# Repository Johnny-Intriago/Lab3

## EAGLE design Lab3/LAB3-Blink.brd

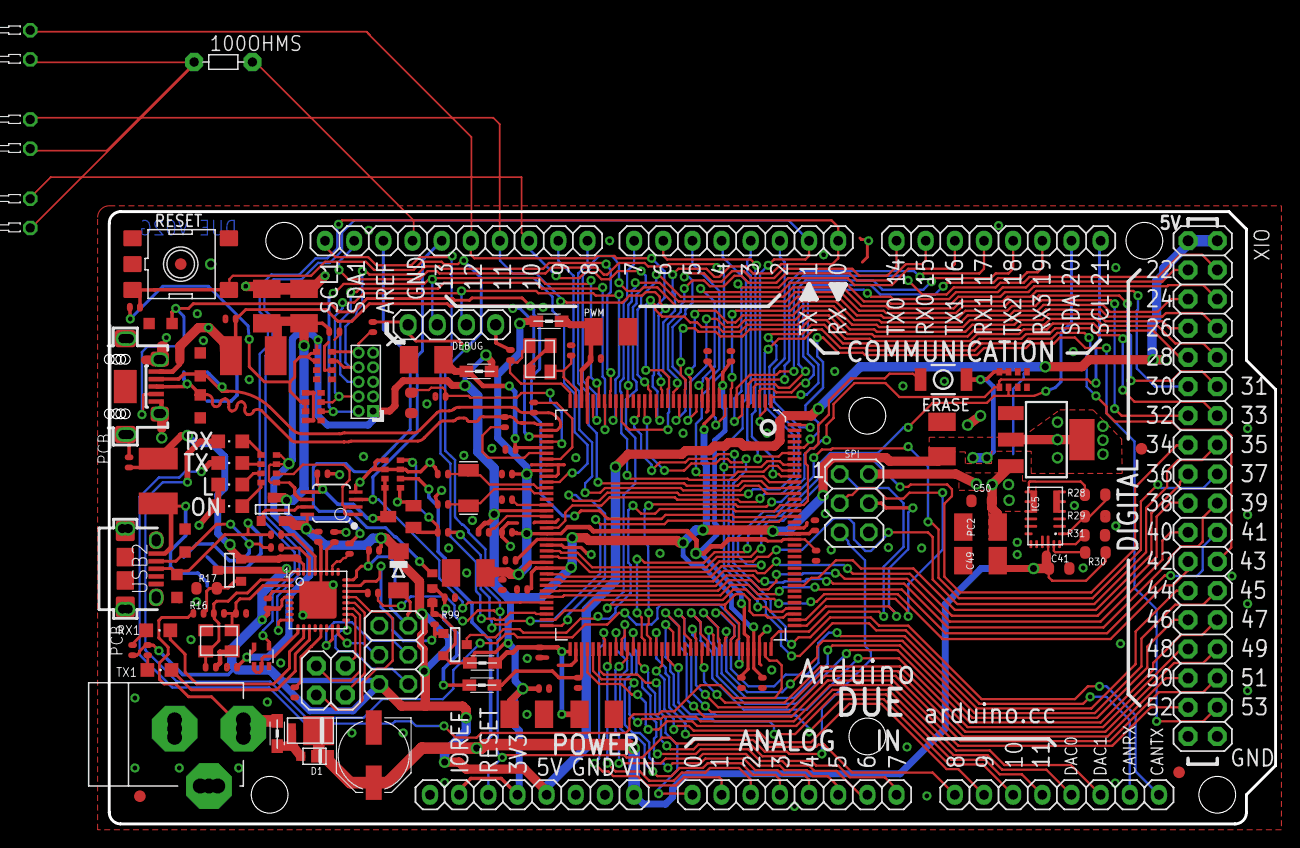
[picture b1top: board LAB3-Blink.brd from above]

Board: 2 copper layers, 101.6 x 53.3 mm, 145 parts (0 on the bottom side), 150 nets.

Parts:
100OHMS: 100; R-5
ADCH: FH254-108DF08500V; 1X08
ADCL: FH254-108DF08500V; 1X08
BR1: NM; J0402
C1, C2, C3, C11, C27, C29, C33, C35, C49: 22uF; SMC_B
C4, C5, C6, C7, C8, C9, C10, C12, C13, C14, C15, C16, C17, C18, C19, C28, C30, C31, C32, C34, C36, C37: 100nF; C0402
C20, C26: 10n; C0402
C21, C22, C23, C24, C25, C39, C40: 22pF; C0402
C38: 1uF; C0402
C41, C50: 100nF; C0603-ROUND
CN2: PINHEAD-2x5-P1.27; PINHEAD_2X05_127
COMMUNICATION: FH254-108DF08500V; 1X08
D1: MSS1P3L-M3/89A; MICROSMP
D2: CD1206-S01575; MINIMELF
D5: SS1P3L; DO220AAL
DEBUG: PH1X4-THT
E$1, E$2, E$3: LED3MM_H7,5MM
ERASE: 157SW; SMD_157SW
F1, F2: MF-MSMF050-2 500mA; L1812
FID1, FID2, FID3, FID4: FIDUCIALMOUNT; FIDUCIA-MOUNT
IC1: LMV358IDGKR; MSOP08
IC4: NX1117CE33Z; SOT223
IC5: MPM3610; QFN-20
IC6: ATMEGA16U2-MU; MLF32
IC10: 74LVC1G125DCKR; SC70-5
ICSP1: ICSP; 2X03
JP5: 2x2M - NM; 2X02
JR1: 0R; R0402
L: Yellow; CHIPLED_0805
L1, L2, L3, L5, L6: MH2029-300Y; 0805
ON: Green; CHIPLED_0805
PC1: 47uF; PANASONIC_D
PC2: 22uF; SMC_B
POWER: FH254-108DF08500V; 1X08
PWMH: FH254-110DF08500V; 1X10
PWML: FH254-108DF08500V; 1X08
Q2: BC847B; SOT23
R1, R8: 0R; R0402
R2, R13, R18, R99: 10K; R0402
R3, R14, R15, R21, R23: 1K; R0402
R4, R16: 100k; R0402
R5, R6: 39R 1%; R0402
R7: 6K8; R0603-ROUND
R9: 1M; R0402
R17: 75K; R0603-ROUND
R19, R20: 22R; R0402
R28: 100K_1%; R0603-ROUND
R29: 19K1_0,1%; R0603-ROUND
R30: 100k; R0603-ROUND
R31: 56k; R0603-ROUND
RESET: TS42
RN1, RN2, RN4: 100k; CAY16
RN3: 1K; CAY16
RN5: 1K5; CAY16
RX, RX1: Yellow; CHIPLED_0805
SPI: ICSP; 2X03
T1, T2, T3: PMV48XP; SOT-23
TX, TX1: Yellow; CHIPLED_0805
U1: ATSAM3X8EA-AU; LQFP144
U$1, U$2: DNP; FRAME
UD+1, UD+2: DNP; TP-1.00MM
UD-1, UD-2: DNP; TP-1.00MM
UGND1, UGND2: DNP; TP-1.00MM
USB1: MCR-AB1-S-RA-SMT-TR; MCR-AB1-S-RA-SMT
USB2: MCR-B-S-RA-SMT-CS1TR; CON2_USB_MICRO_B_AT
UVB1, UVB2: DNP; TP-1.00MM
X2: POWER-SUPPLY; POWERSUPPLY_DC-21MM
XIO: 18x2F-H8.5; 2X18
Y1: 12mHz-12pF-K7; CRYSTAL-3.2-2.5
Y2: 32,768Khz_SMD; RESONATOR_EPSON_FC_145
Y4: 16Mhz-KX-7; CRYSTAL-3.2-2.5
Z1, Z2, Z3, Z4, Z5: BRNCG0603MLC-05E; CT/CN0603

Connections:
8PB4: IC6.18, JP5.1
8PB5: IC6.19, JP5.3
8PB6: IC6.20, JP5.2
8PB7: IC6.21, JP5.4
16U2-TX: IC6.9, IC10.1, IC10.2
+3V3: BR1.3, C1.+, C4.2, C5.2, C6.2, C7.2, C8.2, C18.2, C20.2, C29.+, C37.1, CN2.1, ERASE.1, IC1.6, IC4.2, IC4.4, IC10.5, JR1.1, L1.1, L2.1, POWER.2, POWER.4, R4.2, R99.2, RN1.5, RN1.6, RN2.2, RN2.3, RN3.5, RN3.7, RN3.8, RN5.3, RN5.4, T3.2, U1.11, U1.52, U1.57, U1.62, U1.105, U1.125
+5V: C30.2, C36.1, C50.1, D2.C, IC1.8, IC4.3, IC5.7, IC5.8, IC5.9, IC5.20, IC6.4, IC6.32, ICSP1.2, PC2.+, POWER.5, R13.2, R14.1, R15.1, R28.2, SPI.2, T1.2, T2.1, XIO.1, XIO.2
AD0: ADCL.1, U1.78
AD1: ADCL.2, U1.79
AD2: ADCL.3, U1.80
AD3: ADCL.4, U1.81
AD4: ADCL.5, U1.82
AD5: ADCL.6, U1.83
AD6: ADCL.7, U1.84
AD7: ADCL.8, U1.85
AD8: ADCH.1, U1.88
AD9: ADCH.2, U1.89
AD10: ADCH.3, U1.90
AD11(TXD3): ADCH.4, U1.91
AD14(RXD3): U1.92, XIO.33
AREF: BR1.1, PWMH.8
AVREF: C19.2, L3.2, U1.75
AVREFL: BR1.2, C34.2, JR1.2, L3.1
BD+: R20.2, UD+2.X, USB2.P3, Z4.2
BD-: R19.2, UD-2.X, USB2.P2, Z3.2
CANRX0: ADCH.7, U1.24
CANTX0: ADCH.8, U1.23
CANTX1/IO: U1.140, XIO.34
CMP: C31.2, IC1.5, Q2.3, RN4.3, RN4.4
D+: R6.1, U1.37, UD-1.X, USB1.3, Z1.1
D-: R5.1, U1.38, UD+1.X, USB1.2, Z2.1
DAC0(CANRX1): ADCH.5, U1.76
DAC1: ADCH.6, U1.77
DTR: IC6.13, R18.1
ERASE_CMD: IC6.23, R99.1, T3.3
ERASE_S: ERASE.2, T3.1, U1.130
GATE_CMD: IC1.7, T1.3
GND: C1.-, C2.-, C3.-, C4.1, C5.1, C6.1, C7.1, C8.1, C9.1, C10.1, C11.-, C12.1, C13.1, C14.1, C15.1, C16.1, C17.1, C18.1, C19.1, C21.2, C22.2, C23.2, C24.2, C25.2, C26.2, C27.-, C28.2, C29.-, C30.1, C31.1, C32.1, C33.-, C34.1, C35.-, C36.2, C37.2, C38.2, C39.2, C40.2, C41.2, C49.-, C50.2, CN2.3, CN2.5, CN2.9, DEBUG.1, IC1.4, IC4.1, IC5.3, IC5.12, IC5.13, IC5.14, IC6.3, IC6.28, IC6.33, IC10.3, ICSP1.6, L.C, ON.C, PC1.-, PC2.-, POWER.6, POWER.7, PWMH.7, Q2.2, R2.1, R7.1, R8.1, R17.1, R18.2, R29.1, R31.1, RESET.1, RESET.2, RN1.1, RN1.2, RN1.7, RN1.8, RN2.1, RN2.4, RN2.5, RN2.8, RN4.1, RN4.2, RN4.5, RN4.7, SPI.6, U1.12, U1.33, U1.44, U1.46, U1.54, U1.58, U1.74, U1.106, U1.126, UGND1.X, UGND2.X, USB1.5, USB1.P$1, USB1.P$2, USB1.P$3, USB1.P$4, USB1.P$5, USB1.P$6, USB1.P$7, USB1.P$8, USB1.P$9, USB1.P$10, USB1.P$11, USB1.S1, USB1.S2, USB1.S3, USB1.S4, USB2.P5, USB2.P$1, USB2.P$2, USB2.P$3, USB2.P$4, USB2.P$5, USB2.P$6, USB2.P$7, USB2.P$8, USB2.S1, USB2.S2, USB2.S3, USB2.S4, USB2.S5, USB2.S6, X2.1, X2.3, XIO.35, XIO.36, Y1.2, Y1.4, Y4.2, Y4.4, Z1.2, Z2.2, Z3.1, Z4.1, Z5.1
JTAG_RESET: CN2.10, R1.1, RN1.4
JTAG_TCK: CN2.4, DEBUG.2, RN2.7, U1.28
JTAG_TDI: CN2.8, RN1.3, U1.29
JTAG_TDO: CN2.6, U1.30
JTAG_TMS: CN2.2, DEBUG.3, RN2.6, U1.31
L13: IC1.1, IC1.2, RN3.6
MASTER-RESET: C20.1, DEBUG.4, POWER.3, R1.2, R23.2, RESET.3, RESET.4, SPI.5, U1.47
MISO: SPI.1, U1.108
MISO2: IC6.17, ICSP1.1
MOSI: SPI.4, U1.109
MOSI2: IC6.16, ICSP1.4
unnamed: IC6.26, R21.1
unnamed: L.A, RN3.3
unnamed: ON.A, RN3.4
unnamed: R15.2, RX1.A
unnamed: R8.2, U1.51
unnamed: Q2.1, R3.2, RN4.8
unnamed: R4.1, U1.53
unnamed: D1.A, D5.P$2, L6.1
unnamed: R5.2, U1.43
unnamed: R6.2, U1.42
unnamed: R14.2, TX1.A
unnamed: R16.1, R17.2, T2.3
unnamed: IC5.1, R28.1, R29.2
unnamed: IC5.17, R30.2
unnamed: IC5.18, R31.2
unnamed: RN3.1, RX.A
unnamed: RN3.2, TX.A
PIN22: U1.1, XIO.3
PIN23: U1.7, XIO.4
PIN24: U1.8, XIO.5
PIN25: U1.13, XIO.6
PIN26: U1.14, XIO.7
PIN27: U1.15, XIO.8
PIN28: U1.16, XIO.9
PIN29: U1.19, XIO.10
PIN30: U1.22, XIO.11
PIN31: U1.26, XIO.12
PIN32: U1.32, XIO.13
PIN33: U1.55, XIO.14
PIN34: U1.59, XIO.15
PIN35: U1.60, XIO.16
PIN36: U1.116, XIO.17
PIN37: U1.63, XIO.18
PIN38: U1.64, XIO.19
PIN39: U1.65, XIO.20
PIN40: U1.66, XIO.21
PIN41: U1.67, XIO.22
PIN42: U1.71, XIO.23
PIN43: U1.72, XIO.24
PIN44: U1.101, XIO.25
PIN45: U1.100, XIO.26
PIN46: U1.99, XIO.27
PIN47: U1.98, XIO.28
PIN48: U1.97, XIO.29
PIN49: U1.96, XIO.30
PIN50: U1.95, XIO.31
PIN51: U1.94, XIO.32
PWM2: PWML.3, U1.144
PWM3: PWML.4, U1.139
PWM5: PWML.6, U1.136
PWM6: PWML.7, U1.135
PWM7: PWML.8, U1.134
PWM8: PWMH.1, U1.133
PWM9: PWMH.2, U1.132
PWM11: PWMH.4, U1.20
PWM12: PWMH.5, U1.21
PWM13: IC1.3, PWMH.6, U1.68
RD+: IC6.29, R20.1
RD-: IC6.30, R19.1
RESET2: D2.A, IC6.24, ICSP1.5, R13.1
RESET_CMD: IC6.22, R23.1
RX: IC10.4, PWML.1, U1.27
RXD0: COMMUNICATION.2, U1.18
RXD1: COMMUNICATION.4, U1.5
RXD2: COMMUNICATION.6, U1.3
RXL: RX.C, U1.103
RXL-U2: IC6.10, RX1.C
SCK2: IC6.15, ICSP1.3
SCL0-3: COMMUNICATION.8, RN5.5, U1.87
SCL1: PWMH.10, U1.70
SDA0-3: COMMUNICATION.7, RN5.6, U1.86
SDA1: PWMH.9, U1.9
SPCK: SPI.3, U1.110
SS0/PWM10: PWMH.3, U1.102, U1.111
SS1/PWM4: PWML.5, U1.112, U1.137
TX: IC6.8, PWML.2, U1.2
TXD0: COMMUNICATION.1, U1.17
TXD1: COMMUNICATION.3, U1.6
TXD2: COMMUNICATION.5, U1.4
TXL: TX.C, U1.107
TXL-U2: IC6.11, TX1.C
UOTGID: U1.129, USB1.4, Z5.2
UOTGVBOF: R3.1, U1.128
USBVCC: C27.+, C35.+, F1.1, R2.2, R21.2, T1.1
USBVCCU2: C28.1, F2.1, IC6.31, T2.2
VBG: C25.1, R7.2, U1.40
VDDANA: C3.+, C10.2, L1.2, U1.73
VDDOUT: C11.+, C12.2, C13.2, C14.2, C15.2, C16.2, C17.2, L5.1, U1.10, U1.45, U1.56, U1.61, U1.104, U1.124
VDDOUTMI: C2.+, C9.2, L2.2, U1.41
VDDPLL: C32.2, C33.+, L5.2, U1.34
VIN: C41.1, C49.+, D1.K, D5.P$1, IC5.16, PC1.+, POWER.8, R30.1, RN4.6
VIN+: L6.2, R16.2, X2.2
VUCAP: C38.1, IC6.27
XIN: C22.1, U1.36, Y1.1
XIN32: C24.1, U1.48, Y2.P$2
XOUT: C21.1, U1.35, Y1.3
XOUT32: C23.1, U1.49, Y2.P$1
XT1: C39.1, IC6.1, R9.1, Y4.1
XT2: C40.1, IC6.2, R9.2, Y4.3
XUSB: C26.1, F1.2, U1.39, USB1.1, UVB1.X
XVCC: F2.2, USB2.P1, UVB2.X

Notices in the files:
parts and their libraries:
Arduino-utility: Copyright (c) 2016-2017 Arduino LLC.  All right reserved.
